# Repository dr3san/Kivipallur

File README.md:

# Kivipallur
A split ergo keyboard with a 25 mm thumb trackball.

## Features
- 38 keys
- split, colstag
- diodeless, only 0xCB Helios compatible (good amount of pins, no separate reset switch needed)
- hot-swap Choc v1
- 25 mm trackball with PMW3360 breakout

Layout was created with Ergogen.
I tested it by printing it out on paper and cutting out switch holes from cardboard.

Since I opted for low-profile switches, I also tried a smaller ball, since a ball holder design was available on Thingiverse.
I didn't make a CAD model and due to not accounting for everything in my head, had to modify the holder height a bit.
But it doesn't make it any more uncomfortable to use.

Finding a 25 mm trackball proved difficult, so I tried a steel ball, a silicon nitride ball, and a kids pool set 25 mm ball.
Surprisingly, the pool ball worked best.
Coming from a standard 34 mm ball, I don't feel the smaller ball performs worse.
The trackball sits on 2 mm silicon nitride static bearings. No noticable stiction, friction reasonable for flicks.

QMK config found in my `qmk-userspace` fork.

I started out with 3D printed tenting feet, but moved on to camera mounts.
Bottom plate has M2 holes, which allow for heat-set inserts in addons.
Tenting feet and camera mount attachment with 3D printed thread designed myself.

## Thank-yous
Yowkees for the Keyball

GEIST for the Totem

MrZealot for Ergogen

FlatFootFox for Ergogen tutorials

kepeo for [25 mm trackball holder](https://www.thingiverse.com/thing:6719828)

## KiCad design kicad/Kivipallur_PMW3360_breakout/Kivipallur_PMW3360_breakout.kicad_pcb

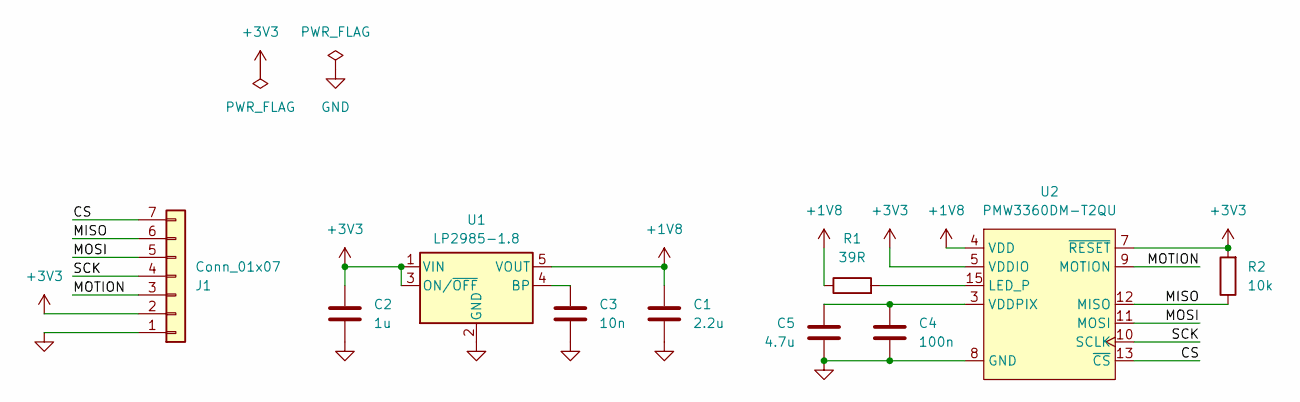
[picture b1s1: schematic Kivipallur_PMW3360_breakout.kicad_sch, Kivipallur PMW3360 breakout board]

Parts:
C1: 2.2u; C_0603_1608Metric_Pad1.08x0.95mm_HandSolder
C2: 1u; C_0603_1608Metric_Pad1.08x0.95mm_HandSolder
C3: 10n; C_0603_1608Metric_Pad1.08x0.95mm_HandSolder
C4: 100n; C_0603_1608Metric_Pad1.08x0.95mm_HandSolder
C5: 4.7u; C_0603_1608Metric_Pad1.08x0.95mm_HandSolder
J1: Conn_01x07; PinHeader_1x07_P2.54mm_Vertical
R1: 39R; R_0603_1608Metric_Pad0.98x0.95mm_HandSolder
R2: 10k; R_0603_1608Metric_Pad0.98x0.95mm_HandSolder
U1: LP2985-1.8; SOT-23-5
U2: PMW3360DM-T2QU; PMW3360DM-T2QU 16Pin

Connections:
+1V8: C1.1, R1.1, U1.5 (VOUT), U2.4 (VDD)
+3V3: C2.1, J1.2, R2.2, U1.1 (VIN), U1.3 (ON/~OFF), U2.5 (VDDIO), U2.7 (~RESET)
/CS: J1.7, U2.13 (~CS)
/MISO: J1.6, R2.1, U2.12 (MISO)
/MOSI: J1.5, U2.11 (MOSI)
/MOTION: J1.3, U2.9 (MOTION)
/SCK: J1.4, U2.10 (SCLK)
GND: C1.2, C2.2, C3.2, C4.1, C5.2, J1.1, U1.2 (GND), U2.8 (GND)
unnamed: C3.1, U1.4 (BP)
unnamed: R1.2, U2.15 (LED_P)
unnamed: C4.2, C5.1, U2.3 (VDDPIX)

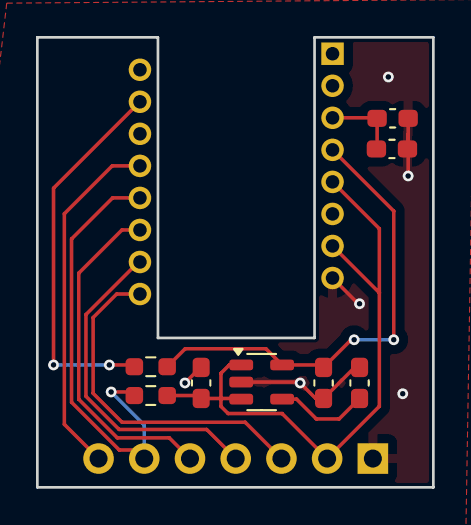
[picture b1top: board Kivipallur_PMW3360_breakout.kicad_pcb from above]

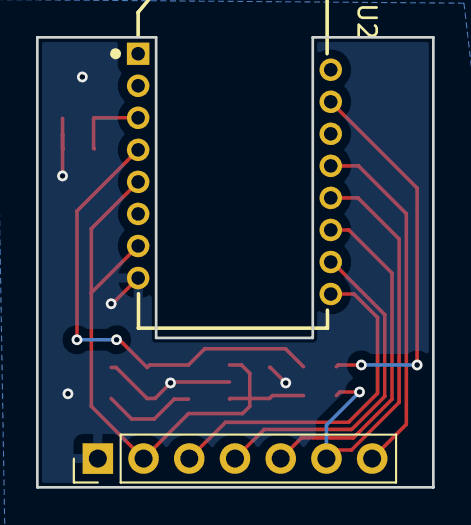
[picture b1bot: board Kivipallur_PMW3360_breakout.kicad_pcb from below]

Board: 2 copper layers, 22.0 x 25.0 mm, 10 parts (2 on the bottom side), 11 nets.

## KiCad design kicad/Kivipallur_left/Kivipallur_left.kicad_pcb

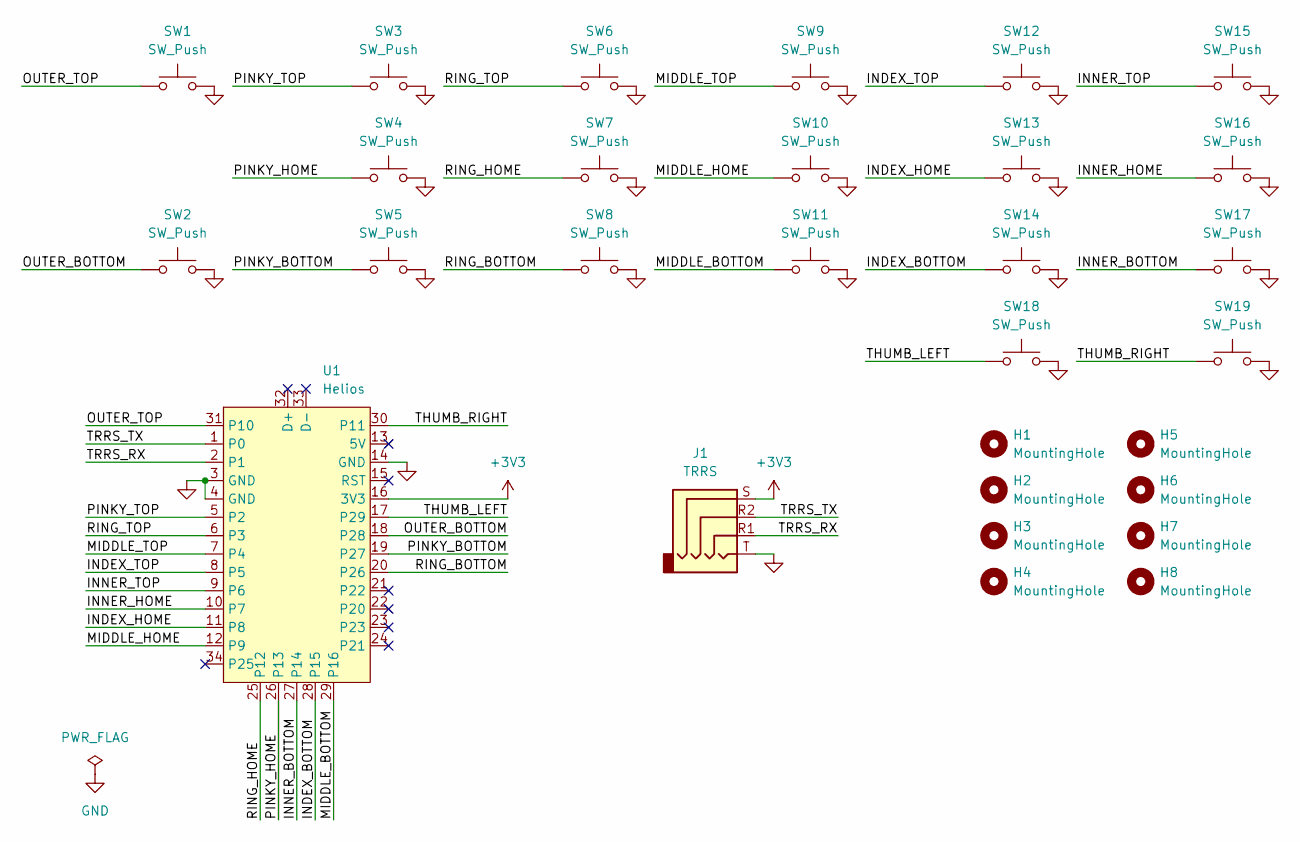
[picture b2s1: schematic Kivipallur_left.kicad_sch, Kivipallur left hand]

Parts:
H1, H2, H3, H4, H5, H6, H7, H8: MountingHole; MountingHole_2.2mm_M2_Pad
J1: TRRS; TRRS-PJ-320A
SW1, SW2, SW3, SW4, SW5, SW6, SW7, SW8, SW9, SW10, SW11, SW12, SW13, SW14, SW15, SW16, SW17, SW18, SW19: SW_Push; Kailh_socket_PG1350_optional
U1: Helios; Helios_ACH

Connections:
+3V3: J1.S, U1.16 (3V3)
/INDEX_BOTTOM: SW14.1, U1.28 (P15)
/INDEX_HOME: SW13.1, U1.11 (P8)
/INDEX_TOP: SW12.1, U1.8 (P5)
/INNER_BOTTOM: SW17.1, U1.27 (P14)
/INNER_HOME: SW16.1, U1.10 (P7)
/INNER_TOP: SW15.1, U1.9 (P6)
/MIDDLE_BOTTOM: SW11.1, U1.29 (P16)
/MIDDLE_HOME: SW10.1, U1.12 (P9)
/MIDDLE_TOP: SW9.1, U1.7 (P4)
/OUTER_BOTTOM: SW2.1, U1.18 (P28)
/OUTER_TOP: SW1.1, U1.31 (P10)
/PINKY_BOTTOM: SW5.1, U1.19 (P27)
/PINKY_HOME: SW4.1, U1.26 (P13)
/PINKY_TOP: SW3.1, U1.5 (P2)
/RING_BOTTOM: SW8.1, U1.20 (P26)
/RING_HOME: SW7.1, U1.25 (P12)
/RING_TOP: SW6.1, U1.6 (P3)
/THUMB_LEFT: SW18.1, U1.17 (P29)
/THUMB_RIGHT: SW19.1, U1.30 (P11)
/TRRS_RX: J1.R1, U1.2 (P1)
/TRRS_TX: J1.R2, U1.1 (P0)
GND: J1.T, SW1.2, SW2.2, SW3.2, SW4.2, SW5.2, SW6.2, SW7.2, SW8.2, SW9.2, SW10.2, SW11.2, SW12.2, SW13.2, SW14.2, SW15.2, SW16.2, SW17.2, SW18.2, SW19.2, U1.3 (GND), U1.4 (GND), U1.14 (GND)

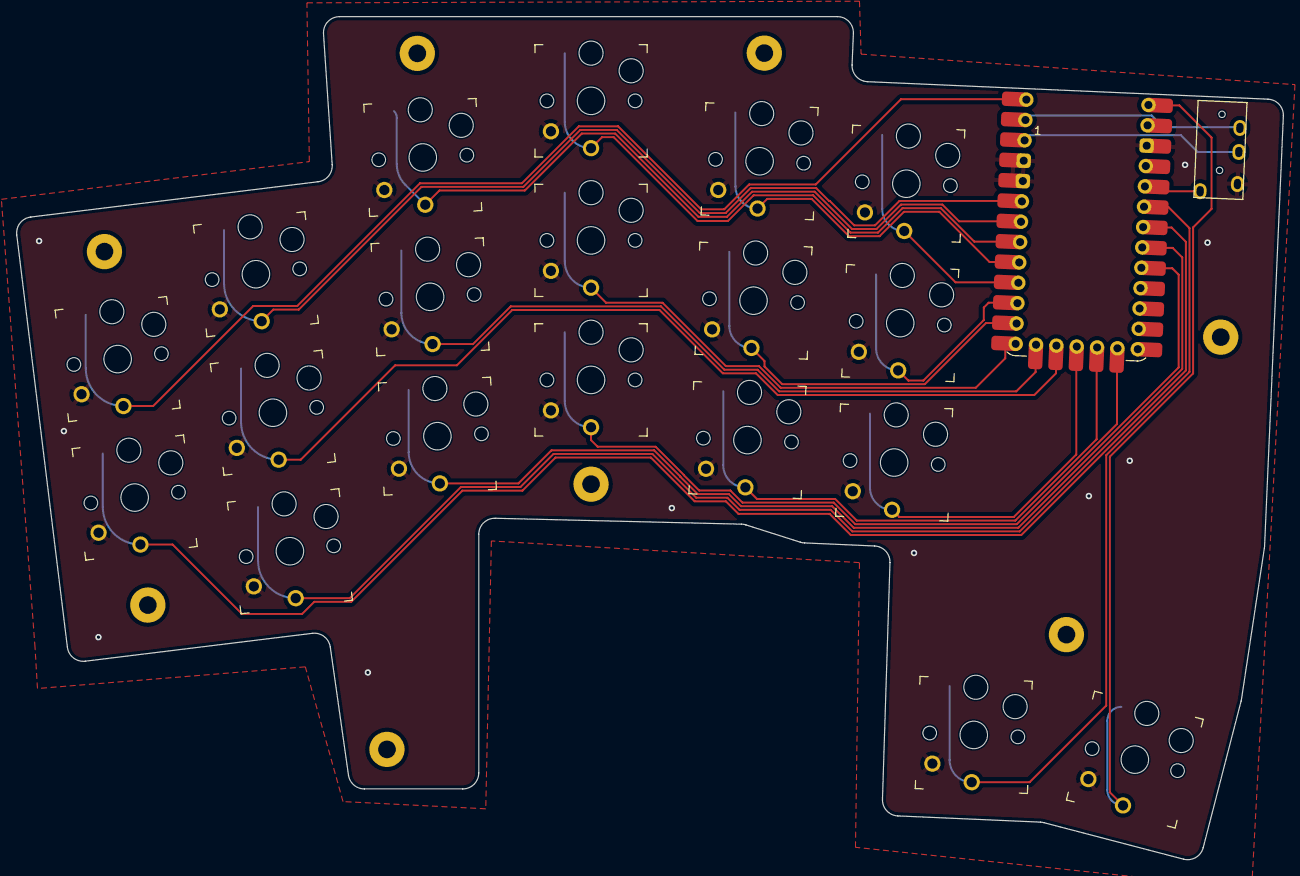
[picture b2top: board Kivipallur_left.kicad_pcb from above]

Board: 2 copper layers, 158.0 x 105.1 mm, 29 parts (0 on the bottom side), 23 nets.

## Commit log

2024-10-03 Add Kicad symbol and footprint libraries, left hand schematic
2024-10-03 Add mounting holes to left hand schematic
2024-10-03 Add unfinished ergogen config
2024-10-03 Add board and plate layout
2024-10-04 Add finished left hand config
2024-10-04 Add left hand PCB design and gerbers
2024-10-07 Add PMW3360 breakout board Kicad project
2024-10-09 Modify ergogen
2024-10-09 Add final ergogen config
2024-10-09 Change bottom plate
2024-10-10 Add bottom plate
2024-10-11 Add left hand PCB
2024-10-13 Add right hand ergogen
2024-10-13 Add right hand schematic and partial PCB
2024-10-14 Add finished right hand PCB
2024-10-14 Add plate PCB
2024-10-14 Revise plate
2024-10-14 Change PMW3360 footprint outline, finalize others
2024-10-14 Add gerbers for all, order 1st prototype
2025-02-07 Add pics, update README
